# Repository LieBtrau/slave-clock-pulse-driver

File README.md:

# slave-clock-pulse-driver
Hardware and firmware to make slave clocks run autonomously

In public offices and vessels slave clocks are used for timekeeping.  These clocks need impulses from a master clock to advance.  To make a slave clock run autonomously, a pulse driver is needed.  That is exactly what the hardware in this project will be doing.

An [MCS-973C1](http://media.wix.com/ugd/56d64c_fa3401d1265442198025946bb6db4be5.pdf) slave clock from Marine Radio Co., Ltd. Korea will equipped with the pulse driver.

# Reading on...
More info can be found on the [Wiki](../../wiki).

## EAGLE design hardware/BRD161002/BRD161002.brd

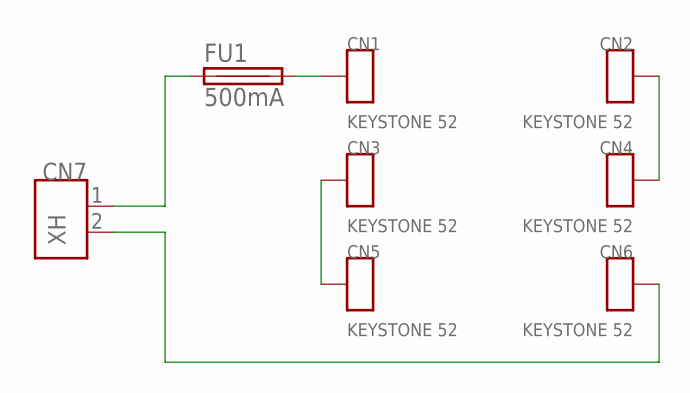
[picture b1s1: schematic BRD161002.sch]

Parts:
CN1, CN2, CN3, CN4, CN5, CN6: KEYSTONE 52; CN_BATTERY_CLIP_A_AA
CN7: XH; CN_HDR1X2_180D_P25_JST_B2B-XH
FU1: 500mA; FU_1812

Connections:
unnamed: CN7.1, FU1.1
unnamed: CN2.1, CN2.2, CN4.1, CN4.2
unnamed: CN3.1, CN3.2, CN5.1, CN5.2
unnamed: CN6.1, CN6.2, CN7.2
unnamed: CN1.1, CN1.2, FU1.2

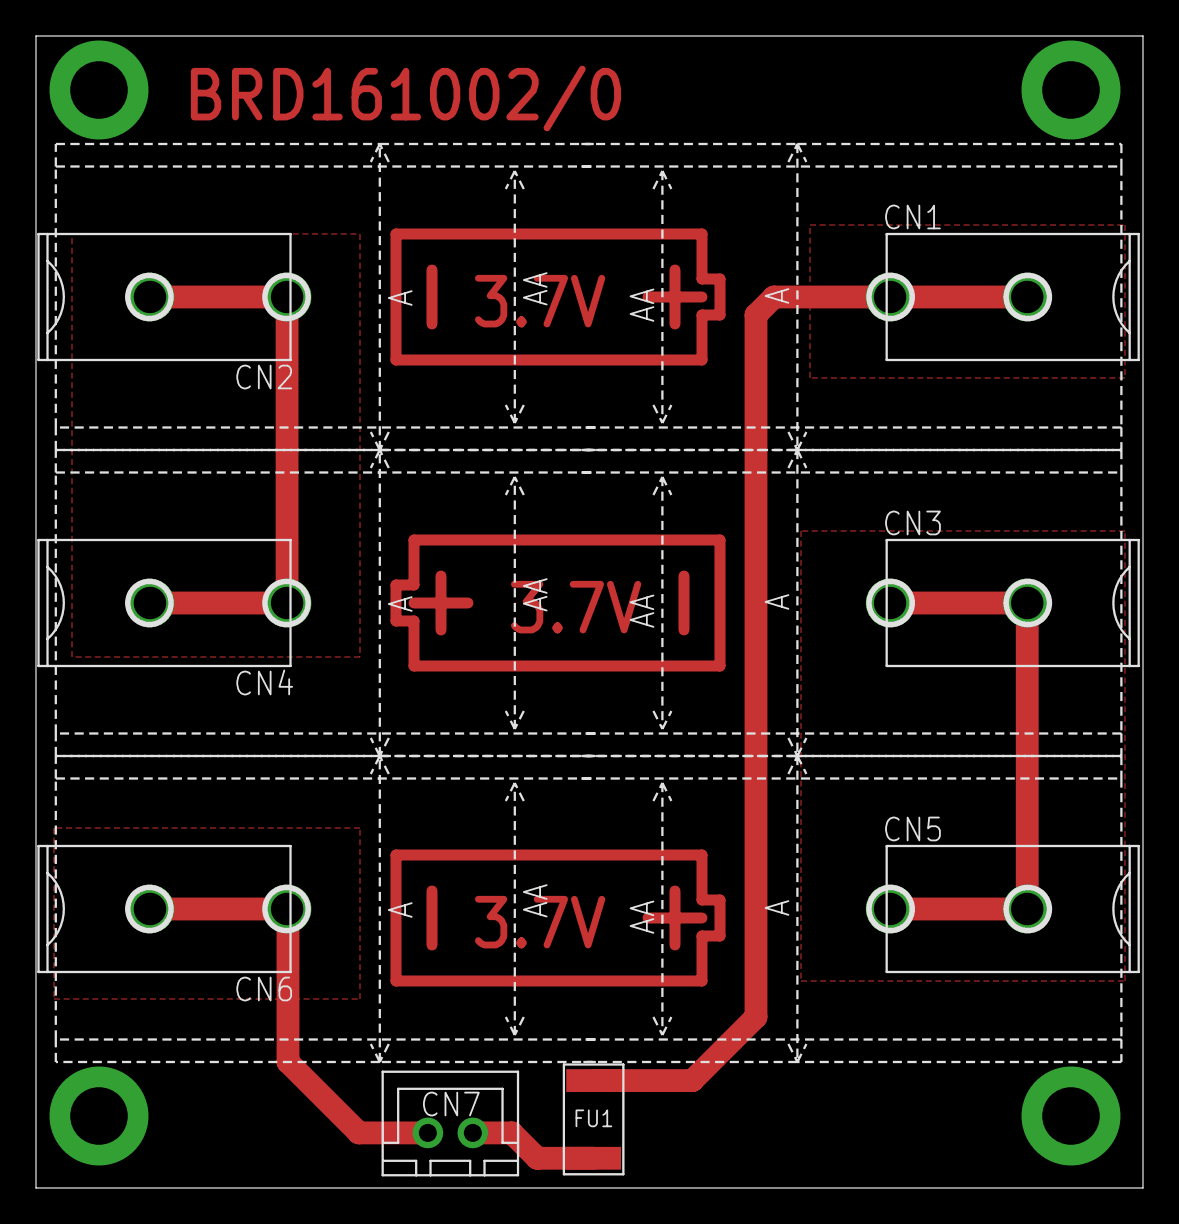
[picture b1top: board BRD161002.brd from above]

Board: 2 copper layers, 61.5 x 64.0 mm, 9 parts (0 on the bottom side), 5 nets.

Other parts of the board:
U$2: FR_FRAME_A5

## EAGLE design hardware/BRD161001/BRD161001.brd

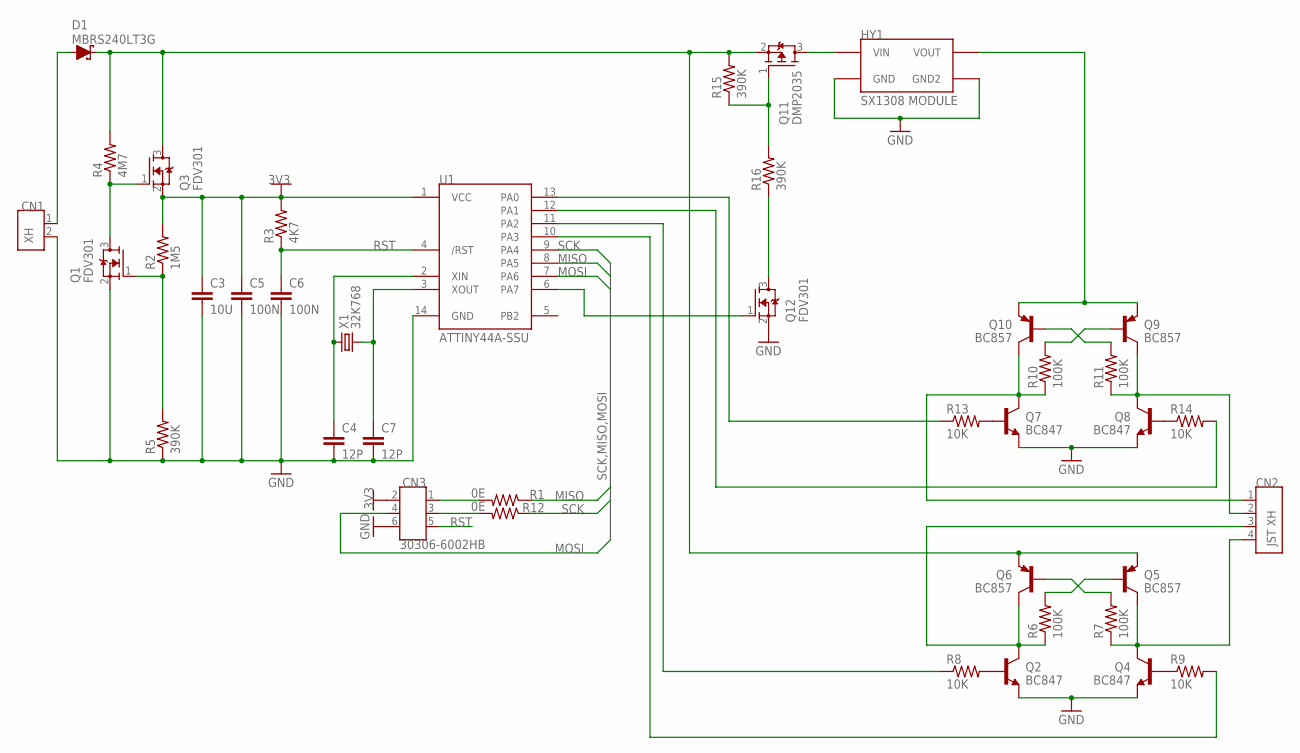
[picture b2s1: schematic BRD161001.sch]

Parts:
C3: 10U; CA_1206
C4, C7: 12P; CA_0603
C5, C6: 100N; CA_1206
CN1: XH; CN_HDR1X2_180D_P25_JST_B2B-XH
CN2: JST XH; CN_HDR1X4_180D_P25_JST_B4B-XH
CN3: 30306-6002HB; CN_HDR2X3_180D_P25_3M
D1: MBRS240LT3G; DI_DO214AA_SMB
HY1: SX1308 MODULE; HY_SX1308
Q1, Q3, Q12: FDV301; SC_SOT23
Q2, Q4, Q7, Q8: BC847; SC_SOT23
Q5, Q6, Q9, Q10: BC857; SC_SOT23
Q11: DMP2035; SC_SOT23
R1, R12: 0E; RE_1206
R2: 1M5; RE_1206
R3: 4K7; RE_1206
R4: 4M7; RE_1206
R5, R15, R16: 390K; RE_1206
R6, R7, R10, R11: 100K; RE_1206
R8, R9, R13, R14: 10K; RE_1206
U1: ATTINY44A-SSU; SC_SO14
X1: 32K768; XT_3215

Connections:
3V3: C3.1, C5.1, CN3.2, Q3.2 (S), R2.2, R3.2, U1.1 (VCC)
GND: C3.2, C4.2, C5.2, C6.2, C7.2, CN1.2, CN3.6, HY1.GND1 (GND), HY1.GND2, Q1.2 (S), Q2.2 (E), Q4.2 (E), Q7.2 (E), Q8.2 (E), Q12.2 (S), R5.1, U1.14 (GND)
MISO: R1.1, U1.8 (PA5)
MOSI: CN3.4, U1.7 (PA6)
unnamed: CN1.1, D1.A
unnamed: D1.C, Q3.3 (D), Q5.2 (E), Q6.2 (E), Q11.2 (S), R4.2, R15.2
unnamed: Q5.1 (B), R6.2
unnamed: Q1.3 (D), Q3.1 (G), R4.1
unnamed: Q6.1 (B), R7.2
unnamed: Q1.1 (G), R2.1, R5.2
unnamed: C4.1, U1.2 (XIN), X1.1
unnamed: CN2.4, Q4.3 (C), Q5.3 (C), R7.1
unnamed: C7.1, U1.3 (XOUT), X1.2
unnamed: CN2.3, Q2.3 (C), Q6.3 (C), R6.1
unnamed: Q2.1 (B), R8.2
unnamed: Q4.1 (B), R9.1
unnamed: HY1.OUT (VOUT), Q9.2 (E), Q10.2 (E)
unnamed: R9.2, U1.10 (PA3)
unnamed: R8.1, U1.11 (PA2)
unnamed: Q9.1 (B), R10.2
unnamed: Q10.1 (B), R11.2
unnamed: Q7.1 (B), R13.2
unnamed: Q8.1 (B), R14.1
unnamed: R14.2, U1.12 (PA1)
unnamed: Q11.1 (G), R15.1, R16.2
unnamed: CN2.2, Q8.3 (C), Q9.3 (C), R11.1
unnamed: CN2.1, Q7.3 (C), Q10.3 (C), R10.1
unnamed: CN3.1, R1.2
unnamed: CN3.3, R12.2
unnamed: R13.1, U1.13 (PA0)
unnamed: Q12.1 (G), U1.6 (PA7)
unnamed: Q12.3 (D), R16.1
unnamed: HY1.VIN, Q11.3 (D)
RST: C6.1, CN3.5, R3.1, U1.4 (/RST)
SCK: R12.1, U1.9 (PA4)

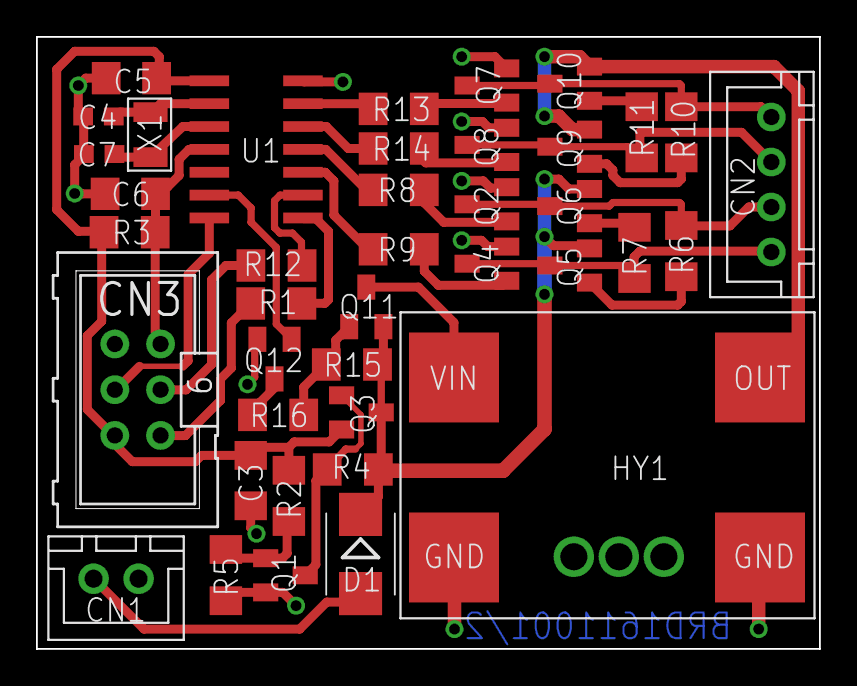
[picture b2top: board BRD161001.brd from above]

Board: 2 copper layers, 43.5 x 34.0 mm, 41 parts (0 on the bottom side), 35 nets.

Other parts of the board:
U$2: FR_FRAME_A5

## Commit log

2016-10-16 Updating readme
2016-10-16 BRD161001 R00.0x
2016-10-23 Interrupt at 1s intervals with control of an output
2016-10-26 Adding clock characteristics
2016-10-26 Updating pulse width
2016-10-26 Driving second hand works
2016-10-29 Updating info about hour/minute hand
2016-10-30 Detailing power consumption
2016-10-31 updating battery technology
2016-11-01 Moving hardware data to wiki
2016-11-06 Updating requirements
2016-11-06 Adding link to the Wiki
2016-11-06 Correcting wiki link
2016-11-13 R1 of the hardware design
2016-11-28 updating pulse widths
2016-11-29 typo
2016-11-30 Build for checking length of timing pulses.
2016-12-02 Working version, fully interrupt driven
2016-12-02 working on R2 of PCB
2016-12-02 R2 of BRD161001
2016-12-04 R0 of battery pack
2016-12-05 Moving less interesting data to wiki
2017-01-02 Disabling pulse skipping
2017-01-02 Updating outdated links
